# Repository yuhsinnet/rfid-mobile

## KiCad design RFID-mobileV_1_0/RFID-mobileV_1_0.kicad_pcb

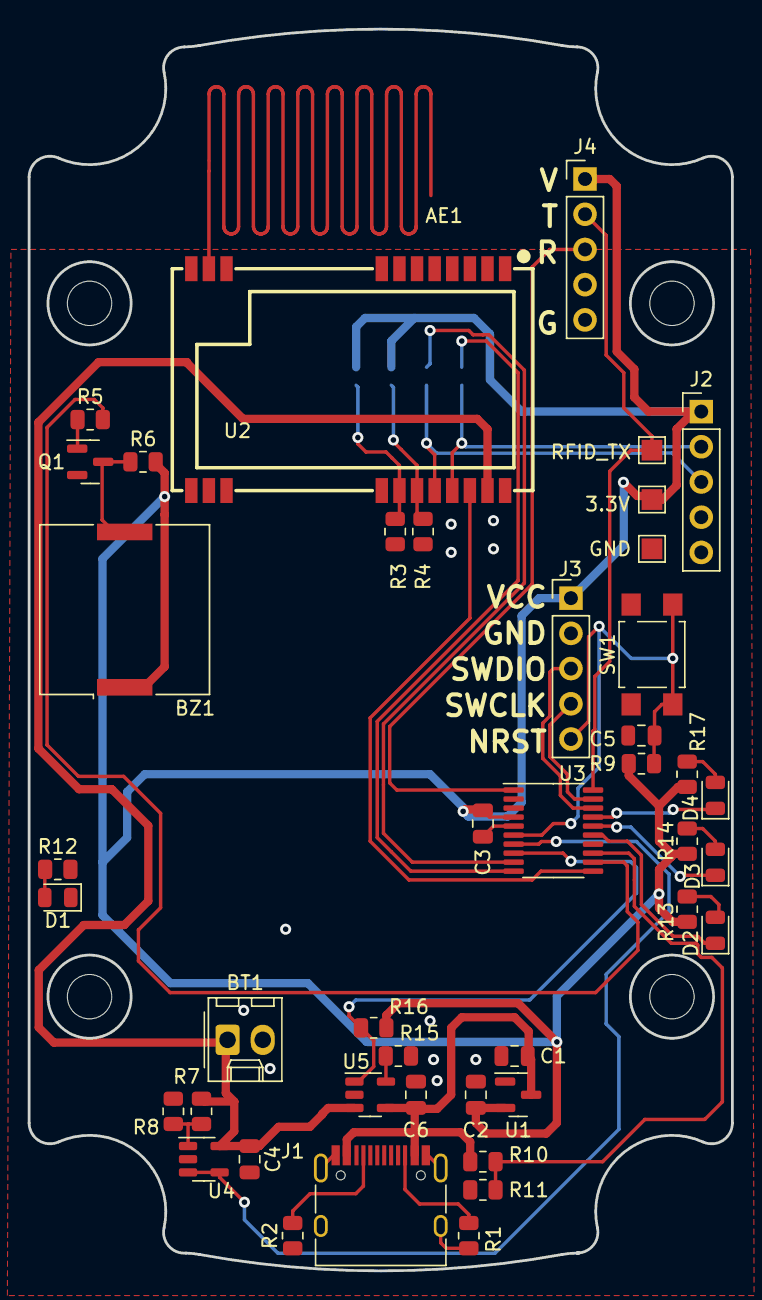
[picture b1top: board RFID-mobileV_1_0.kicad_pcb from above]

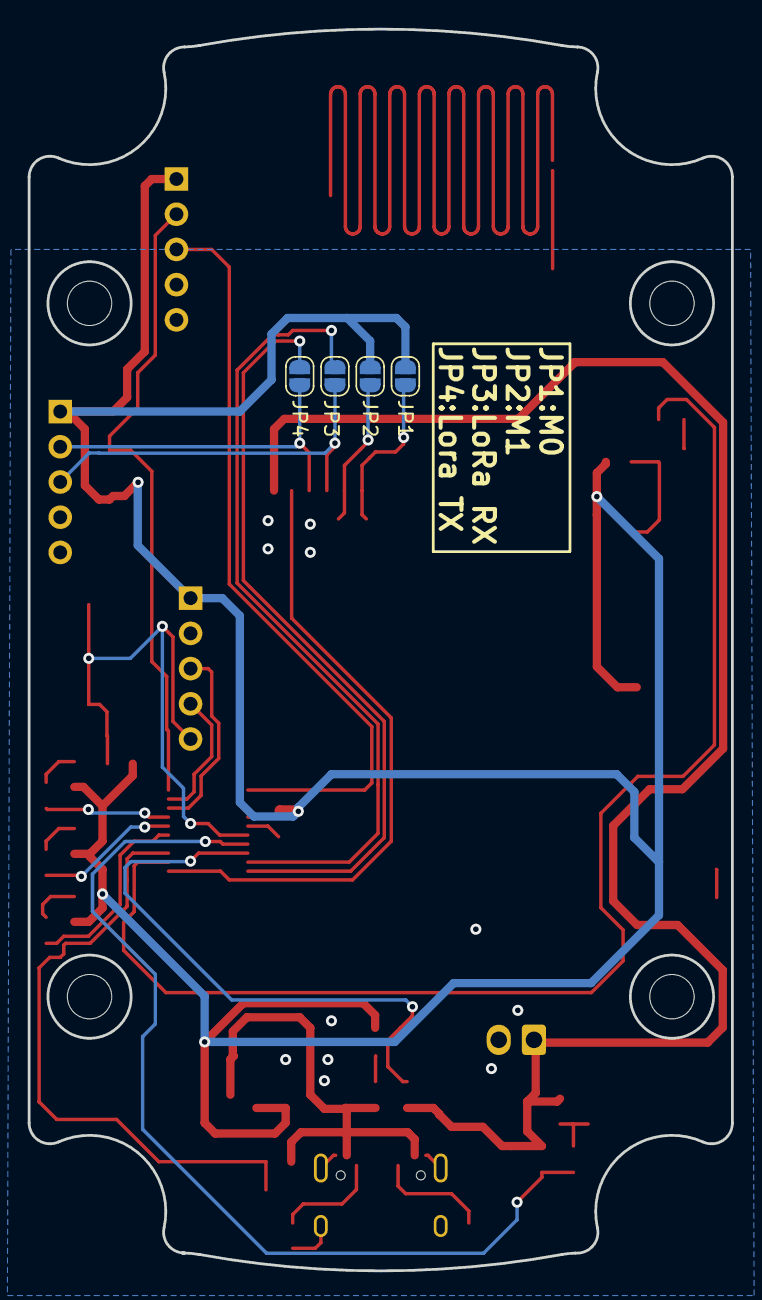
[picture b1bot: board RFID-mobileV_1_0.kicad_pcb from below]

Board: 2 copper layers, 50.7 x 89.5 mm, 52 parts (4 on the bottom side), 34 nets.

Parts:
AE1: Antenna; 433MHz_V
BT1: Battery; Molex_KK-254_AE-6410-02A_1x02_P2.54mm_Vertical
BZ1: Buzzer; Buzzer_Murata_PKLCS1212E
C1, C2, C3, C4, C5, C6: 0.1uF; C_0805_2012Metric
D1: PWR; LED_0805_2012Metric
D2, D3, D4: LED; LED_0805_2012Metric
H1, H2, H3, H4: MountingHole; MountingHole_3.2mm_M3
J1: USB_C_Receptacle_USB2.0; USB_C_Receptacle_HRO_TYPE-C-31-M-12
J2, J4: Conn_01x05_Male; PinHeader_1x05_P2.54mm_Vertical
J3: Conn_01x05_Female; PinHeader_1x05_P2.54mm_Vertical
JP1, JP2, JP3, JP4: SolderJumper_2_Open; SolderJumper-2_P1.3mm_Open_RoundedPad1.0x1.5mm
Q1: MMBT3904; SOT-23
R1, R2: 5K1; R_0805_2012Metric
R3, R4, R6, R13, R14, R17: 1k; R_0805_2012Metric
R5: 22k; R_0805_2012Metric
R7, R8: 2M; R_0805_2012Metric
R9, R16: 10k; R_0805_2012Metric
R10: 47k; R_0805_2012Metric
R11: 91k; R_0805_2012Metric
R12: 330; R_0805_2012Metric
R15: 1.65K; R_0805_2012Metric
SW1: SW_Push; SW_SPST_TL3305A
TP1: RFID_TX; TestPoint_Pad_1.5x1.5mm
TP2: 3.3V; TestPoint_Pad_1.5x1.5mm
TP3: GND; TestPoint_Pad_1.5x1.5mm
U1: XC6206P332MR; SOT-23
U2: E22-400T22S; E220-400TxxS
U3: STM32G030FxP; TSSOP-20_4.4x6.5mm_P0.65mm
U4: LM321; SOT-23-5
U5: TP4054; TSOT-23-5

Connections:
+3V3: BZ1.1 (-), C2.1, C3.1, J2.1, J3.1, J4.1, JP1.2 (B), JP2.2 (B), R6.2, R9.1, R12.2, R13.2, R14.2, R16.1, R17.2, TP2.1, U1.2 (VO), U3.4 (VDD/VDDA)
+5V: C1.1, C6.1, J1.A4 (VBUS), J1.A9 (VBUS), J1.B4 (VBUS), J1.B9 (VBUS), R10.1, U1.3 (VI), U5.4 (VCC)
+BATT: BT1.1 (+), C4.1, R7.1, U2.25 (VCC), U4.5 (V+), U5.3 (BAT)
/ANT: AE1.1 (A), U2.12 (ANT)
/BATT_moint: U3.7 (PA0), U4.3 (-), U4.4
/CC1: J1.A5 (CC1), R2.2
/CC2: J1.B5 (CC2), R1.2
/CHAR_STAT: R16.2, U3.8 (PA1), U5.1 (~CHRG)
/LoRa_AUX: U2.24 (AUX), U3.11 (PA4)
/LoRa_RXD: JP3.2 (B), U3.9 (PA2)
/LoRa_RXD_: J2.3, JP3.1 (A), U2.22 (RXD)
/LoRa_TXD: JP4.2 (B), U3.10 (PA3)
/LoRa_TXD_: J2.2, JP4.1 (A), U2.23 (TXD)
/M0: JP1.1 (A), R3.2, U2.20 (M0)
/M1: JP2.1 (A), R4.2, U2.21 (M1)
/NRST: C5.1, J3.5, R9.2, SW1.2, U3.6 (NRST)
/PA8: D2.1 (K), U3.15 (PB0/PB1/PB2/PA8)
/PA9: D3.1 (K), U3.16 (PA11[PA9])
/PA10: D4.1 (K), U3.17 (PA12[PA10])
/RFID_RXD_: J4.3, U3.1 (PB7/PB8)
/RFID_TXD_: J4.2, TP1.1, U3.20 (PB3/PB4/PB5/PB6)
/SWCLK: J3.4, U3.19 (PA15/PA14-BOOT0)
/SWDIO: J3.3, U3.18 (PA13)
/VBUS_sing: R10.2, R11.1, U3.13 (PA6)
/buz: R5.2, U3.12 (PA5)
GND: BT1.2 (-), C1.2, C2.2, C3.2, C4.2, C5.2, C6.2, D1.1 (K), J1.A1 (GND), J1.A12 (GND), J1.B1 (GND), J1.B12 (GND), J1.S1 (SHIELD), J2.5, J3.2, J4.5, Q1.2 (E), R1.1, R2.1, R3.1, R4.1, R8.2, R11.2, R15.2, SW1.1, TP3.1, U1.1 (GND), U2.2 (GND), U2.8 (GND), U2.11 (GND), U2.13 (GND), U2.14 (GND), U2.15 (GND), U2.16 (GND), U2.19 (GND), U2.26 (GND), U3.5 (VSS/VSSA), U4.2 (V-), U5.2 (GND)
unnamed: BZ1.2 (+), Q1.3 (C), R6.1
unnamed: D1.2 (A), R12.1
unnamed: D2.2 (A), R13.1
unnamed: D3.2 (A), R14.1
unnamed: D4.2 (A), R17.1
unnamed: Q1.1 (B), R5.1
unnamed: R7.2, R8.1, U4.1 (+)
unnamed: R15.1, U5.5 (PROG)

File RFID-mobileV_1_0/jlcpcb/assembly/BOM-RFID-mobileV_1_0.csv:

Comment,Designator,Footprint,LCSC
Buzzer,BZ1,Buzzer_Murata_PKLCS1212E,C113159
91k,R11,R_0805_2012Metric,C137484
10k,"R16,R9",R_0805_2012Metric,C17414
1k,"R13,R14,R17,R3,R4,R6",R_0805_2012Metric,C17513
22k,R5,R_0805_2012Metric,C17560
330,R12,R_0805_2012Metric,C17630
47k,R10,R_0805_2012Metric,C17713
PWR,D1,LED_0805_2012Metric,C2296
2M,"R7,R8",R_0805_2012Metric,C26112
USB_C_Receptacle_USB2.0,J1,USB_C_Receptacle_HRO_TYPE-C-31-M-12,C2765186
5K1,"R1,R2",R_0805_2012Metric,C27834
1.65K,R15,R_0805_2012Metric,C322308
TP4054,U5,TSOT-23-5,C32574
SW_Push,SW1,SW_SPST_TL3305A,C480315
0.1uF,"C1,C2,C3,C4,C5,C6",C_0805_2012Metric,C49678
STM32G030FxP,U3,TSSOP-20_4.4x6.5mm_P0.65mm,C529330
XC6206P332MR,U1,SOT-23,C5446
LM321,U4,SOT-23-5,C7972
LED,"D2,D3,D4",LED_0805_2012Metric,C84256
MMBT3904,Q1,SOT-23,C909754

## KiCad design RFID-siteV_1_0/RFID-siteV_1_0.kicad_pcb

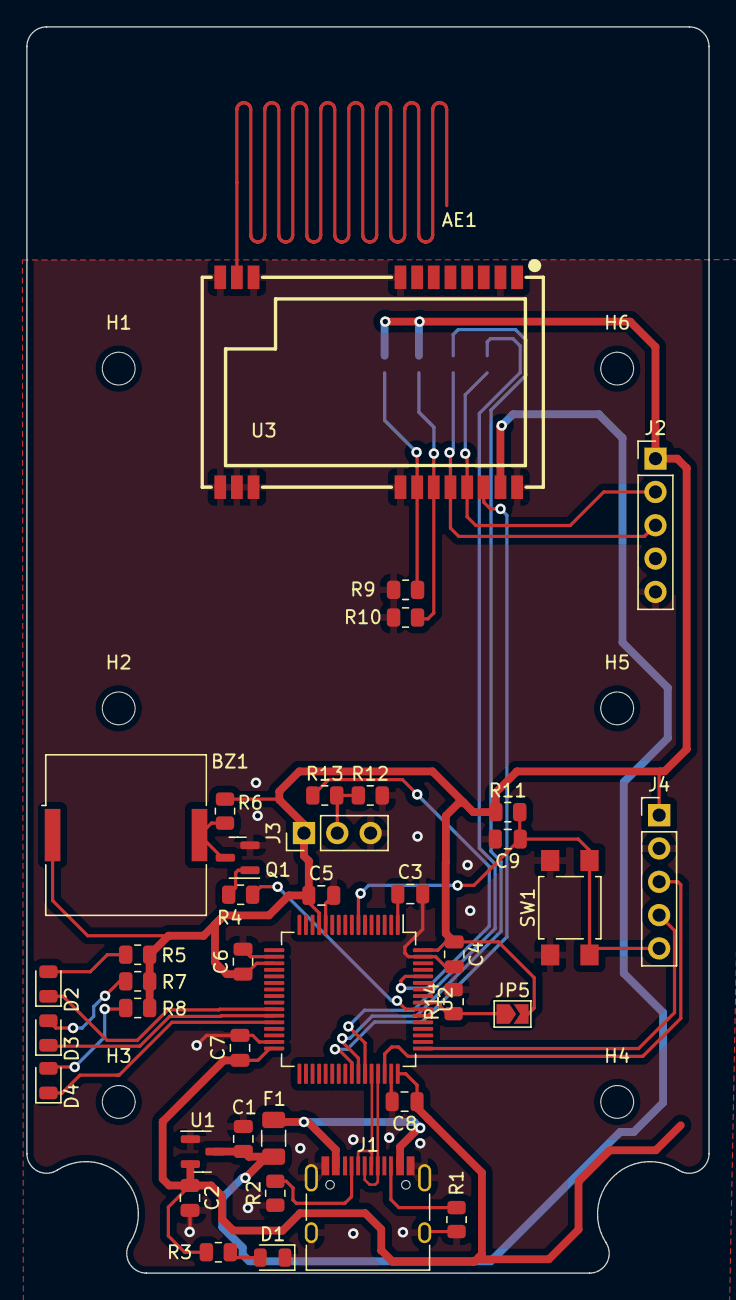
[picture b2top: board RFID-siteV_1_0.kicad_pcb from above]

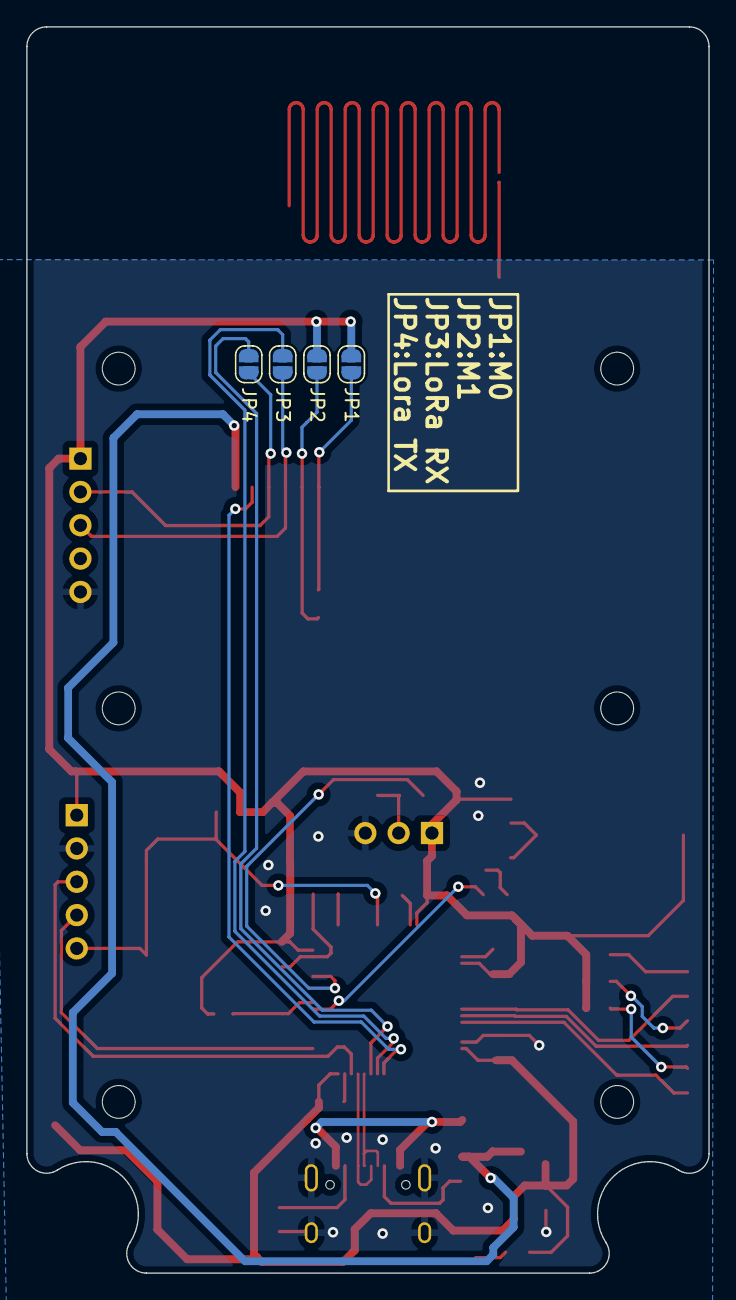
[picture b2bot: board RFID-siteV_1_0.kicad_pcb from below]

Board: 2 copper layers, 52.0 x 95.0 mm, 50 parts (4 on the bottom side), 33 nets.

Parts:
AE1: Antenna; 433MHz_V
BZ1: Buzzer; Buzzer_Murata_PKLCS1212E
C1, C2, C3, C4, C5, C6, C7, C8, C9: 0.1uF; C_0805_2012Metric
D1: PWR; LED_0805_2012Metric
D2, D3, D4: LED; LED_0805_2012Metric
F1: Fuse 200mA; Fuse_1206_3216Metric
H1, H2, H3, H4, H5, H6: MountingHole; MountingHole_2.5mm
J1: USB_C_Receptacle_USB2.0; USB_C_Receptacle_HRO_TYPE-C-31-M-12
J2: Conn_01x05_Male; PinHeader_1x05_P2.54mm_Vertical
J3: Conn_01x03_Male; PinHeader_1x03_P2.54mm_Vertical
J4: Conn_01x05_Female; PinHeader_1x05_P2.54mm_Vertical
JP1, JP2, JP3, JP4: SolderJumper_2_Open; SolderJumper-2_P1.3mm_Open_RoundedPad1.0x1.5mm
JP5: SolderJumper_2_Open; SolderJumper-2_P1.3mm_Open_TrianglePad1.0x1.5mm
Q1: MMBT3904; SOT-23
R1, R2: 5K1; R_0805_2012Metric
R3: 330; R_0805_2012Metric
R4: 22k; R_0805_2012Metric
R5, R6, R7, R8, R9, R10, R13, R14: 1k; R_0805_2012Metric
R11: 10k; R_0805_2012Metric
R12: 0R; R_0805_2012Metric
SW1: SW_Push; SW_SPST_TL3305A
U1: XC6206P332MR; SOT-23
U2: STM32L053R8Tx; LQFP-64_10x10mm_P0.5mm
U3: E22-400T22S; E220-400TxxS

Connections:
+3V3: BZ1.1 (-), C2.1, C4.1, C5.1, C6.1, C7.1, C8.1, J2.1, J3.1, J4.1, JP1.2 (B), JP2.2 (B), JP5.2 (B), R3.2, R5.2, R6.2, R7.2, R8.2, R11.1, U1.2 (VO), U2.13 (VDDA), U2.19 (VDD), U2.32 (VDD), U2.48 (VDD_USB), U2.64 (VDD)
+5V: C1.1, F1.1, U1.3 (VI), U3.25 (VCC)
/ANT: AE1.1 (A), U3.12 (ANT)
/BOOT0: R13.1, U2.60 (BOOT0)
/CC1: J1.A5 (CC1), R2.2
/CC2: J1.B5 (CC2), R1.2
/L53R8_UART1_RX: JP4.2 (B), U2.43 (PA10)
/L53R8_UART1_TX: JP3.2 (B), U2.42 (PA9)
/LoRa_AUX: U2.41 (PA8), U3.24 (AUX)
/LoRa_RXD_: J2.3, JP3.1 (A), U3.22 (RXD)
/LoRa_TXD_: J2.2, JP4.1 (A), U3.23 (TXD)
/M0: JP1.1 (A), R9.2, U3.20 (M0)
/M1: JP2.1 (A), R10.2, U3.21 (M1)
/NRST: C9.1, J4.5, R11.2, SW1.2, U2.7 (NRST)
/PB0: D2.1 (K), U2.26 (PB0)
/PB1: D3.1 (K), U2.27 (PB1)
/PB2: D4.1 (K), U2.28 (PB2)
/SWCLK: J4.4, U2.49 (PA14)
/SWDIO: J4.3, U2.46 (PA13)
/USB_D+: J1.A6 (D+), J1.B6 (D+), U2.45 (PA12)
/USB_D-: J1.A7 (D-), J1.B7 (D-), U2.44 (PA11)
/buz: R4.2, U2.55 (PB3)
/mod_sel: JP5.1 (A), R14.1, U2.56 (PB4)
GND: C1.2, C2.2, C3.2, C4.2, C5.2, C6.2, C7.2, C8.2, C9.2, D1.1 (K), J1.A1 (GND), J1.A12 (GND), J1.B1 (GND), J1.B12 (GND), J1.S1 (SHIELD), J2.5, J3.3, J4.2, Q1.2 (E), R1.1, R2.1, R9.1, R10.1, R12.2, R14.2, SW1.1, U1.1 (GND), U2.12 (VSSA), U2.18 (VSS), U2.31 (VSS), U2.47 (VSS), U2.63 (VSS), U3.2 (GND), U3.8 (GND), U3.11 (GND), U3.13 (GND), U3.14 (GND), U3.15 (GND), U3.16 (GND), U3.19 (GND), U3.26 (GND)
unnamed: BZ1.2 (+), Q1.3 (C), R6.1
unnamed: C3.1, U2.1 (VLCD)
unnamed: D1.2 (A), R3.1
unnamed: D2.2 (A), R5.1
unnamed: D3.2 (A), R7.1
unnamed: D4.2 (A), R8.1
unnamed: F1.2, J1.A4 (VBUS), J1.A9 (VBUS), J1.B4 (VBUS), J1.B9 (VBUS)
unnamed: J3.2, R12.1, R13.2
unnamed: Q1.1 (B), R4.1

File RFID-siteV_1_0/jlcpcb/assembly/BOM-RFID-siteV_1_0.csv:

Comment,Designator,Footprint,LCSC
Buzzer,BZ1,Buzzer_Murata_PKLCS1212E,C113159
10k,R11,R_0805_2012Metric,C17414
0R,R12,R_0805_2012Metric,C17477
1k,"R10,R13,R5,R6,R7,R8,R9",R_0805_2012Metric,C17513
22k,R4,R_0805_2012Metric,C17560
330,R3,R_0805_2012Metric,C17630
MMBT3904,Q1,SOT-23,C20526
USB_C_Receptacle_USB2.0,J1,USB_C_Receptacle_HRO_TYPE-C-31-M-12,C2765186
5K1,"R1,R2",R_0805_2012Metric,C27834
SW_Push,SW1,SW_SPST_TL3305A,C480315
0.1uF,"C1,C2,C3,C4,C5,C6,C7,C8,C9",C_0805_2012Metric,C49678
XC6206P332MR,U1,SOT-23,C5446
Fuse 200mA,F1,Fuse_1206_3216Metric,C69680
PWR,D1,LED_0805_2012Metric,C72043
STM32L053R8Tx,U2,LQFP-64_10x10mm_P0.5mm,C79207
LED,"D2,D3,D4",LED_0805_2012Metric,C84256

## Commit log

2022-04-20 add type-c
2022-04-21 增加電池管理IC
2022-04-21 update sch
2022-04-23 add ign update sch
2022-04-23 Update RFID-mobileV_1_0.kicad_sch
    AUX pin
2022-04-24 add board edge
2022-04-24 Update fp-info-cache
2022-04-28 Update RFID-mobileV_1_0.kicad_pcb
    remove Case box
2022-04-29 add
    PCB Broad edge
    place Device
2022-04-29 pcb update
2022-04-29 update
    remote DW02
2022-04-29 add jlcpcb
2022-04-30 create site
2022-04-30 site
2022-05-01 Update RFID-siteV_1_0.kicad_sch
    add boot 0 select pin
2022-05-01 add PCB
2022-05-01 Update RFID-siteV_1_0.kicad_sch
    SWD
2022-05-01 jlcpcb
2022-05-02 fix BT1
2022-05-17 add todo.txt
2022-06-02 Update RFID-siteV_1_0.kicad_pcb
    V1.ST-LINK 腳位上下顛倒，接腳不便使用。
    V2.缺少模式(加符號&不加符號)選擇接點。
2022-06-02 Update RFID-siteV_1_0.kicad_sch
    add 模式選擇點(jump)
2022-06-02 Update RFID-mobileV_1_0.kicad_sch
    V2.RFID 通信腳位使用錯誤(TX RX 交換)。
    V3.電源3.3V 應由電池端供電，不能由5V 供電。
2022-06-02 case
